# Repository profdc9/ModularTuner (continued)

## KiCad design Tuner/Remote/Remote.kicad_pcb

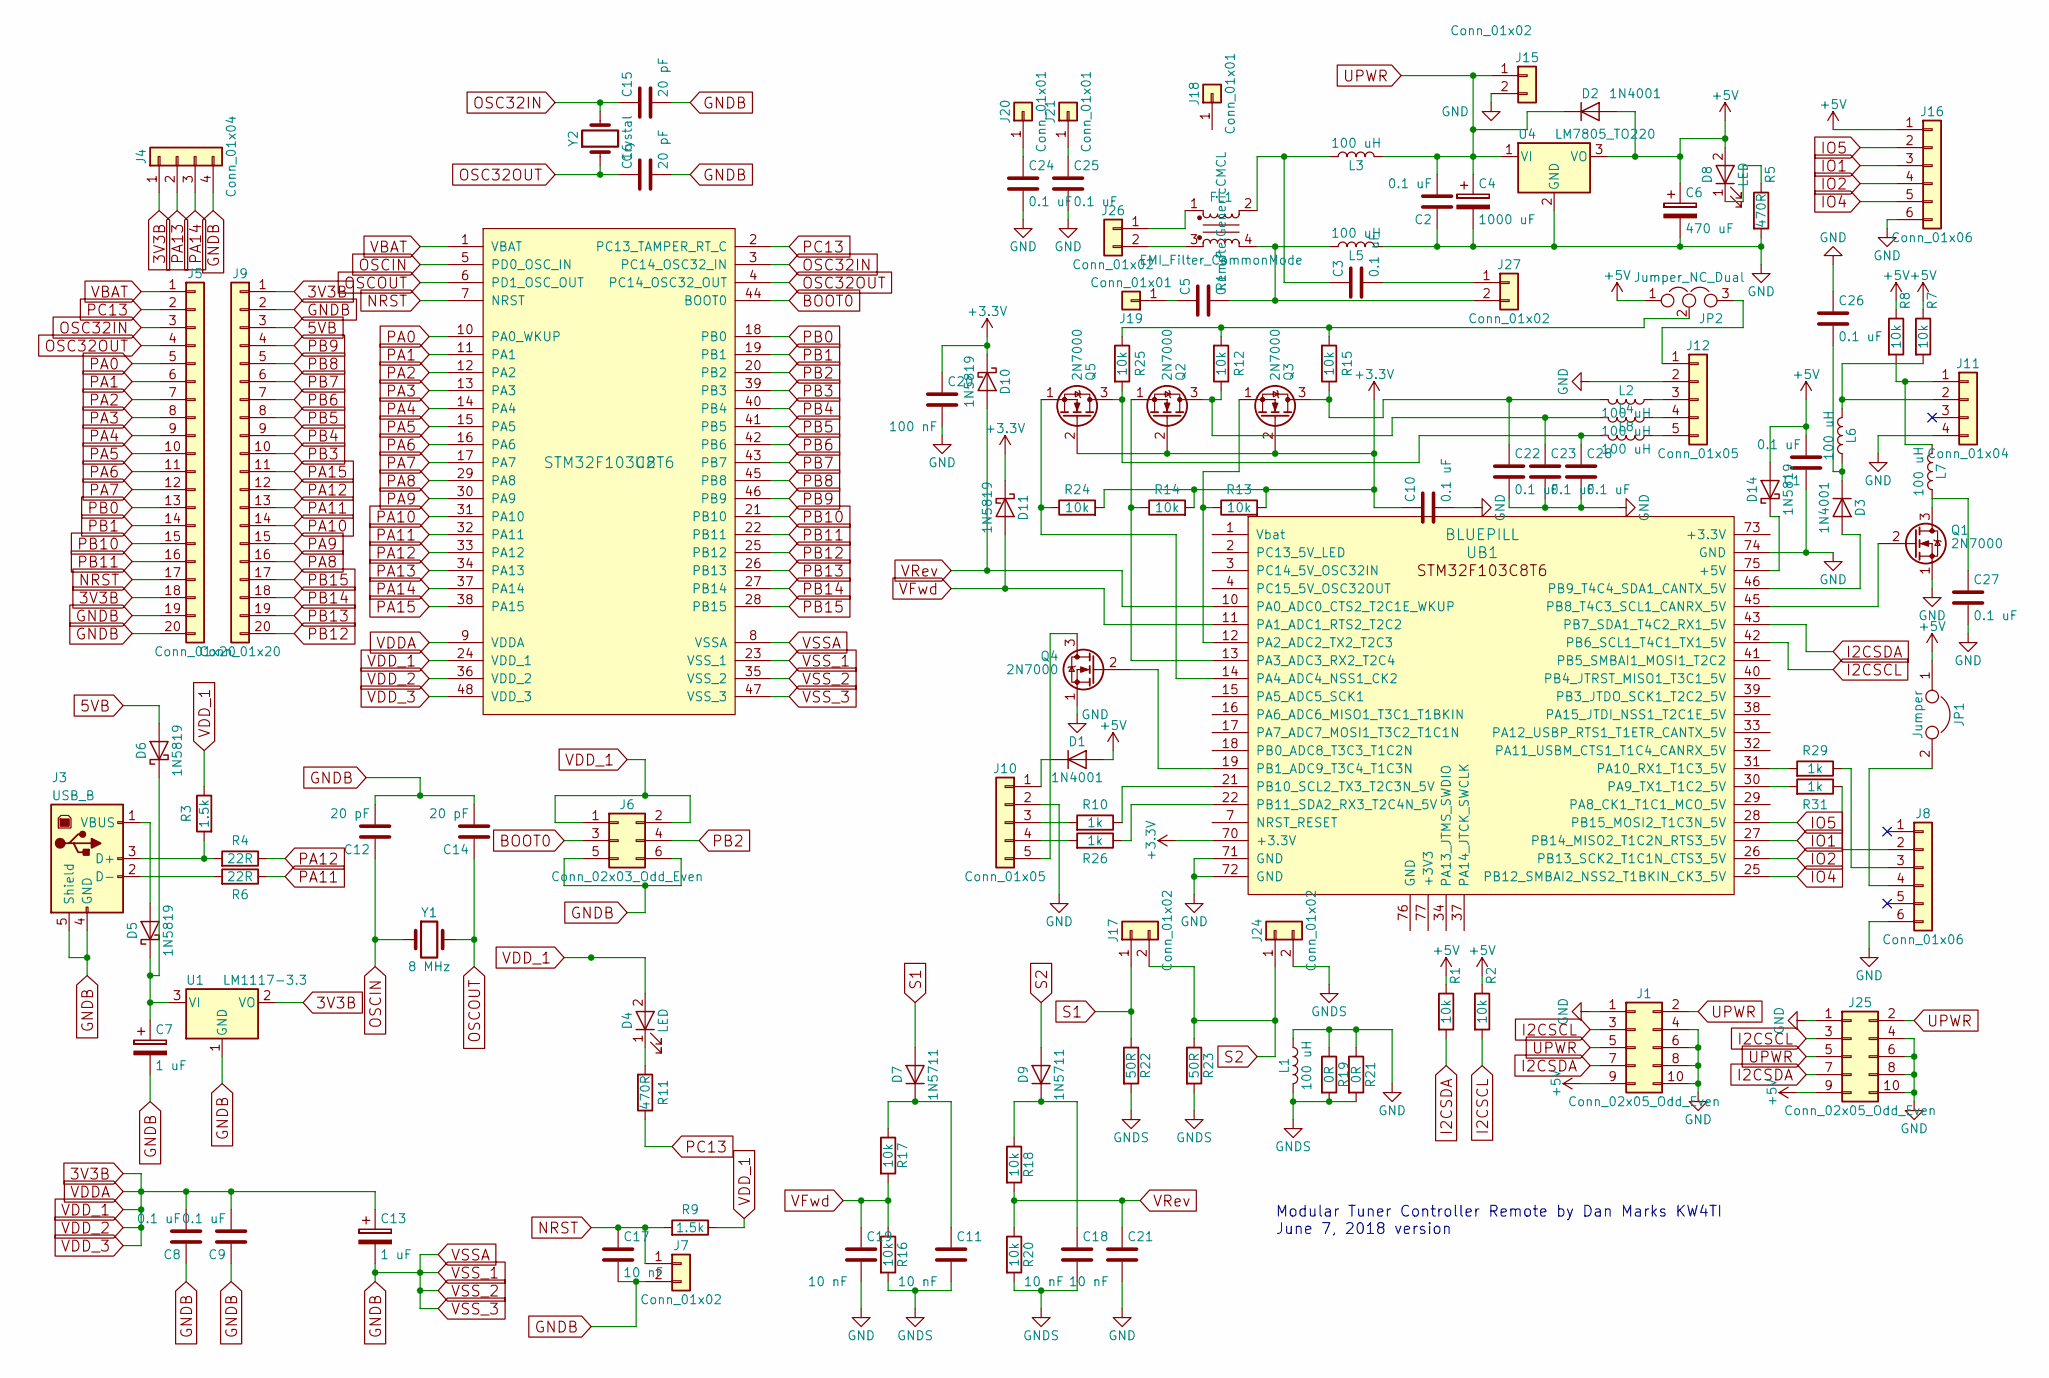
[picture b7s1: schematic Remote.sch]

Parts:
C1, C2, C8, C9, C10, C22, C23, C24, C25, C26, C27, C28: 0.1 uF; C_Disc_D5.0mm_W2.5mm_P2.50mm
C3, C5: 0.1 uF; C_Disc_D12.0mm_W4.4mm_P7.75mm
C4: 1000 uF; CP_Radial_D18.0mm_P7.50mm
C6: 470 uF; CP_Radial_D10.0mm_P5.00mm
C7, C13: 1 uF; CP_Radial_D5.0mm_P2.50mm
C11, C17, C18, C19, C21: 10 nF; C_Disc_D5.0mm_W2.5mm_P2.50mm
C12, C14, C15, C16: 20 pF; C_Disc_D5.0mm_W2.5mm_P2.50mm
C20: 100 nF; C_Disc_D5.0mm_W2.5mm_P2.50mm
D1, D2, D3: 1N4001; D_DO-41_SOD81_P7.62mm_Horizontal
D4: LED; LED_D3.0mm
D5, D6, D10, D11, D14: 1N5819; D_DO-41_SOD81_P7.62mm_Horizontal
D7, D9: 1N5711; D_DO-35_SOD27_P7.62mm_Horizontal
D8: LED; LED_D5.0mm
FL1: EMI_Filter_CommonMode; GenericCMCL
J1, J25: Conn_02x05_Odd_Even; Pin_Header_Straight_2x05_Pitch2.54mm
J3: USB_B
J4, J11: Conn_01x04; Pin_Header_Straight_1x04_Pitch2.54mm
J5, J9: Conn_01x20; Pin_Header_Straight_1x20_Pitch2.54mm
J6: Conn_02x03_Odd_Even; Pin_Header_Straight_2x03_Pitch2.54mm
J7: Conn_01x02; SW_PUSH_6mm
J8, J16: Conn_01x06; Pin_Header_Straight_1x06_Pitch2.54mm
J10, J12: Conn_01x05; Pin_Header_Straight_1x05_Pitch2.54mm
J15, J17, J24, J26, J27: Conn_01x02; TerminalBlock_bornier-2_P5.08mm
J18, J19, J20, J21: Conn_01x01; 1pin
JP1: Jumper; Pin_Header_Straight_1x02_Pitch2.54mm
JP2: Jumper_NC_Dual; Pin_Header_Straight_1x03_Pitch2.54mm
L1: 100 uH; L_Axial_L9.5mm_D4.0mm_P15.24mm_Horizontal_Fastron_SMCC
L2, L4, L6, L7, L8: 100 uH; L_Axial_L5.3mm_D2.2mm_P7.62mm_Horizontal_Vishay_IM-1
L3, L5: 100 uH; L_Toroid_Vertical_L14.0mm_W6.3mm_P4.57mm_Pulse_A
Q1, Q2, Q3, Q4, Q5: 2N7000; TO-92_Molded_Narrow
R1, R2, R7, R8, R12, R13, R14, R15, R16, R17, R18, R20, R24, R25: 10k; R_Axial_DIN0207_L6.3mm_D2.5mm_P7.62mm_Horizontal
R3, R9: 1.5k; R_Axial_DIN0207_L6.3mm_D2.5mm_P7.62mm_Horizontal
R4, R6: 22R; R_Axial_DIN0207_L6.3mm_D2.5mm_P7.62mm_Horizontal
R5, R11: 470R; R_Axial_DIN0207_L6.3mm_D2.5mm_P7.62mm_Horizontal
R10, R26, R29, R31: 1k; R_Axial_DIN0207_L6.3mm_D2.5mm_P7.62mm_Horizontal
R19, R21: 0R; R_Axial_DIN0207_L6.3mm_D2.5mm_P7.62mm_Horizontal
R22, R23: 50R; R_Axial_DIN0309_L9.0mm_D3.2mm_P12.70mm_Horizontal
U1: LM1117-3.3; TO-220-3_Vertical
U2: STM32F103C8T6; LQFP-48_7x7mm_Pitch0.5mm
U4: LM7805_TO220; TO-220-3_Vertical
UB1: BLUEPILL
Y1: 8 MHz; Crystal_HC49-U_Vertical
Y2: Crystal; Crystal_Round_d2.0mm_Vertical

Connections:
3V3B: C8.2, C9.2, C13.1, D4.2 (A), J4.1, J5.18, J6.1, J6.2, J9.1, R3.1, R9.1, U1.2 (VO), U2.9 (VDDA), U2.24 (VDD_1), U2.36 (VDD_2), U2.48 (VDD_3)
5VB: D6.2 (A), J9.3
+3V3: C10.1, C20.1, D10.1 (K), D11.1 (K), Q2.2 (G), Q3.2 (G), Q5.2 (G), R13.2, R14.2, R24.2, UB1.70 (+3.3V)
+5V: C1.2, C6.1, D1.2 (A), D2.2 (A), D8.2 (A), D14.2 (A), J1.9, J16.1, J25.9, JP1.1, JP2.1, R1.1, R2.1, R7.1, R8.1, U4.3 (VO)
BOOT0: J6.3, U2.44 (BOOT0)
GND: C1.1, C2.1, C4.2, C6.2, C10.2, C19.2, C20.2, C21.2, C22.2, C23.2, C24.2, C25.2, C26.1, C27.2, C28.2, J1.1, J1.4, J1.6, J1.8, J1.10, J8.6, J10.2, J11.4, J12.2, J15.2, J16.6, J25.1, J25.4, J25.6, J25.8, J25.10, L1.1, L5.2, Q1.1 (S), Q4.1 (S), R5.2, R19.1, R21.1, U4.2 (GND), UB1.71 (GND), UB1.72 (GND), UB1.74 (GND)
GNDB: C7.2, C8.1, C9.1, C12.2, C13.2, C14.2, C15.2, C16.2, C17.2, J3.4 (GND), J3.5 (Shield), J4.4, J5.19, J5.20, J6.5, J6.6, J7.2, J9.2, U1.1 (GND), U2.8 (VSSA), U2.23 (VSS_1), U2.35 (VSS_2), U2.47 (VSS_3)
GNDS: C11.2, C18.2, J24.2, L1.2, R16.2, R19.2, R20.2, R21.2, R22.2, R23.2
I2CSCL: J1.3, J25.3, R2.2, UB1.42 (PB6_SCL1_T4C1_TX1_5V)
I2CSDA: J1.7, J25.7, R1.2, UB1.43 (PB7_SDA1_T4C2_RX1_5V)
IO1: J16.3, UB1.27 (PB14_MISO2_T1C2N_RTS3_5V)
IO2: J16.4, UB1.26 (PB13_SCK2_T1C1N_CTS3_5V)
IO4: J16.5, UB1.25 (PB12_SMBAI2_NSS2_T1BKIN_CK3_5V)
IO5: J16.2, UB1.28 (PB15_MOSI2_T1C3N_5V)
NRST: C17.1, J5.17, J7.1, R9.2, U2.7 (NRST)
unnamed: C3.1, FL1.2, L3.1
unnamed: C3.2, J27.1
unnamed: C5.1, J19.1
unnamed: C5.2, FL1.4, J27.2, L5.1
unnamed: C7.1, D5.1 (K), D6.1 (K), U1.3 (VI)
unnamed: C11.1, D7.1 (K), R17.1
unnamed: C18.1, D9.1 (K), R18.1
unnamed: C22.1, L2.2, Q3.3 (D), R15.1
unnamed: C23.1, L4.2, Q2.3 (D), R12.1
unnamed: C24.1, J20.1
unnamed: C25.1, J21.1
unnamed: C26.2, D3.1 (K), L6.1
unnamed: C27.1, L7.1, Q1.3 (D)
unnamed: C28.1, L8.2, Q5.3 (D), R25.2
unnamed: D1.1 (K), J10.1
unnamed: D3.2 (A), UB1.46 (PB9_T4C4_SDA1_CANTX_5V)
unnamed: D4.1 (K), R11.2
unnamed: D5.2 (A), J3.1 (VBUS)
unnamed: D8.1 (K), R5.1
unnamed: D14.1 (K), UB1.75 (+5V)
unnamed: FL1.1, J26.1
unnamed: FL1.3, J26.2
unnamed: J3.2 (D-), R6.2
unnamed: J3.3 (D+), R3.2, R4.2
unnamed: J8.2, R31.1
unnamed: J8.3, R29.1
unnamed: J8.4, JP1.2
unnamed: J10.3, R10.2
unnamed: J10.4, R26.2
unnamed: J10.5, Q4.3 (D)
unnamed: J11.1, L7.2, R8.2
unnamed: J11.2, L6.2, R7.2
unnamed: J12.1, JP2.3
unnamed: J12.3, L2.1
unnamed: J12.4, L4.1
unnamed: J12.5, L8.1
unnamed: JP2.2, R12.2, R15.2, R25.1
unnamed: Q1.2 (G), UB1.45 (PB8_T4C3_SCL1_CANRX_5V)
unnamed: Q2.1 (S), R14.1, UB1.13 (PA3_ADC3_RX2_T2C4)
unnamed: Q3.1 (S), R13.1, UB1.12 (PA2_ADC2_TX2_T2C3)
unnamed: Q4.2 (G), UB1.19 (PB1_ADC9_T3C4_T1C3N)
unnamed: Q5.1 (S), R24.1, UB1.14 (PA4_ADC4_NSS1_CK2)
unnamed: R10.1, UB1.21 (PB10_SCL2_TX3_T2C3N_5V)
unnamed: R26.1, UB1.22 (PB11_SDA2_RX3_T2C4N_5V)
unnamed: R29.2, UB1.31 (PA10_RX1_T1C3_5V)
unnamed: R31.2, UB1.30 (PA9_TX1_T1C2_5V)
OSC32IN: C15.1, J5.3, U2.3 (PC14_OSC32_IN), Y2.2
OSC32OUT: C16.1, J5.4, U2.4 (PC14_OSC32_OUT), Y2.1
OSCIN: C12.1, U2.5 (PD0_OSC_IN), Y1.1
OSCOUT: C14.1, U2.6 (PD1_OSC_OUT), Y1.2
PA0: J5.5, U2.10 (PA0_WKUP)
PA1: J5.6, U2.11 (PA1)
PA2: J5.7, U2.12 (PA2)
PA3: J5.8, U2.13 (PA3)
PA4: J5.9, U2.14 (PA4)
PA5: J5.10, U2.15 (PA5)
PA6: J5.11, U2.16 (PA6)
PA7: J5.12, U2.17 (PA7)
PA8: J9.16, U2.29 (PA8)
PA9: J9.15, U2.30 (PA9)
PA10: J9.14, U2.31 (PA10)
PA11: J9.13, R6.1, U2.32 (PA11)
PA12: J9.12, R4.1, U2.33 (PA12)
PA13: J4.2, U2.34 (PA13)
PA14: J4.3, U2.37 (PA14)
PA15: J9.11, U2.38 (PA15)
PB0: J5.13, U2.18 (PB0)
PB1: J5.14, U2.19 (PB1)
PB2: J6.4, U2.20 (PB2)
PB3: J9.10, U2.39 (PB3)
PB4: J9.9, U2.40 (PB4)
PB5: J9.8, U2.41 (PB5)
PB6: J9.7, U2.42 (PB6)
PB7: J9.6, U2.43 (PB7)
PB8: J9.5, U2.45 (PB8)
PB9: J9.4, U2.46 (PB9)
PB10: J5.15, U2.21 (PB10)
PB11: J5.16, U2.22 (PB11)
PB12: J9.20, U2.25 (PB12)
PB13: J9.19, U2.26 (PB13)
PB14: J9.18, U2.27 (PB14)
PB15: J9.17, U2.28 (PB15)
PC13: J5.2, R11.1, U2.2 (PC13_TAMPER_RT_C)
S1: D7.2 (A), J17.1, R22.1
S2: D9.2 (A), J17.2, J24.1, R23.1
UPWR: C2.2, C4.1, D2.1 (K), J1.2, J1.5, J15.1, J25.2, J25.5, L3.2, U4.1 (VI)
VBAT: J5.1, U2.1 (VBAT)
VFwd: C19.1, D11.2 (A), R16.1, R17.2, UB1.11 (PA1_ADC1_RTS2_T2C2)
VRev: C21.1, D10.2 (A), R18.2, R20.1, UB1.10 (PA0_ADC0_CTS2_T2C1E_WKUP)

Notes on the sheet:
Modular Tuner Controller Remote by Dan Marks KW4TI June 7, 2018 version

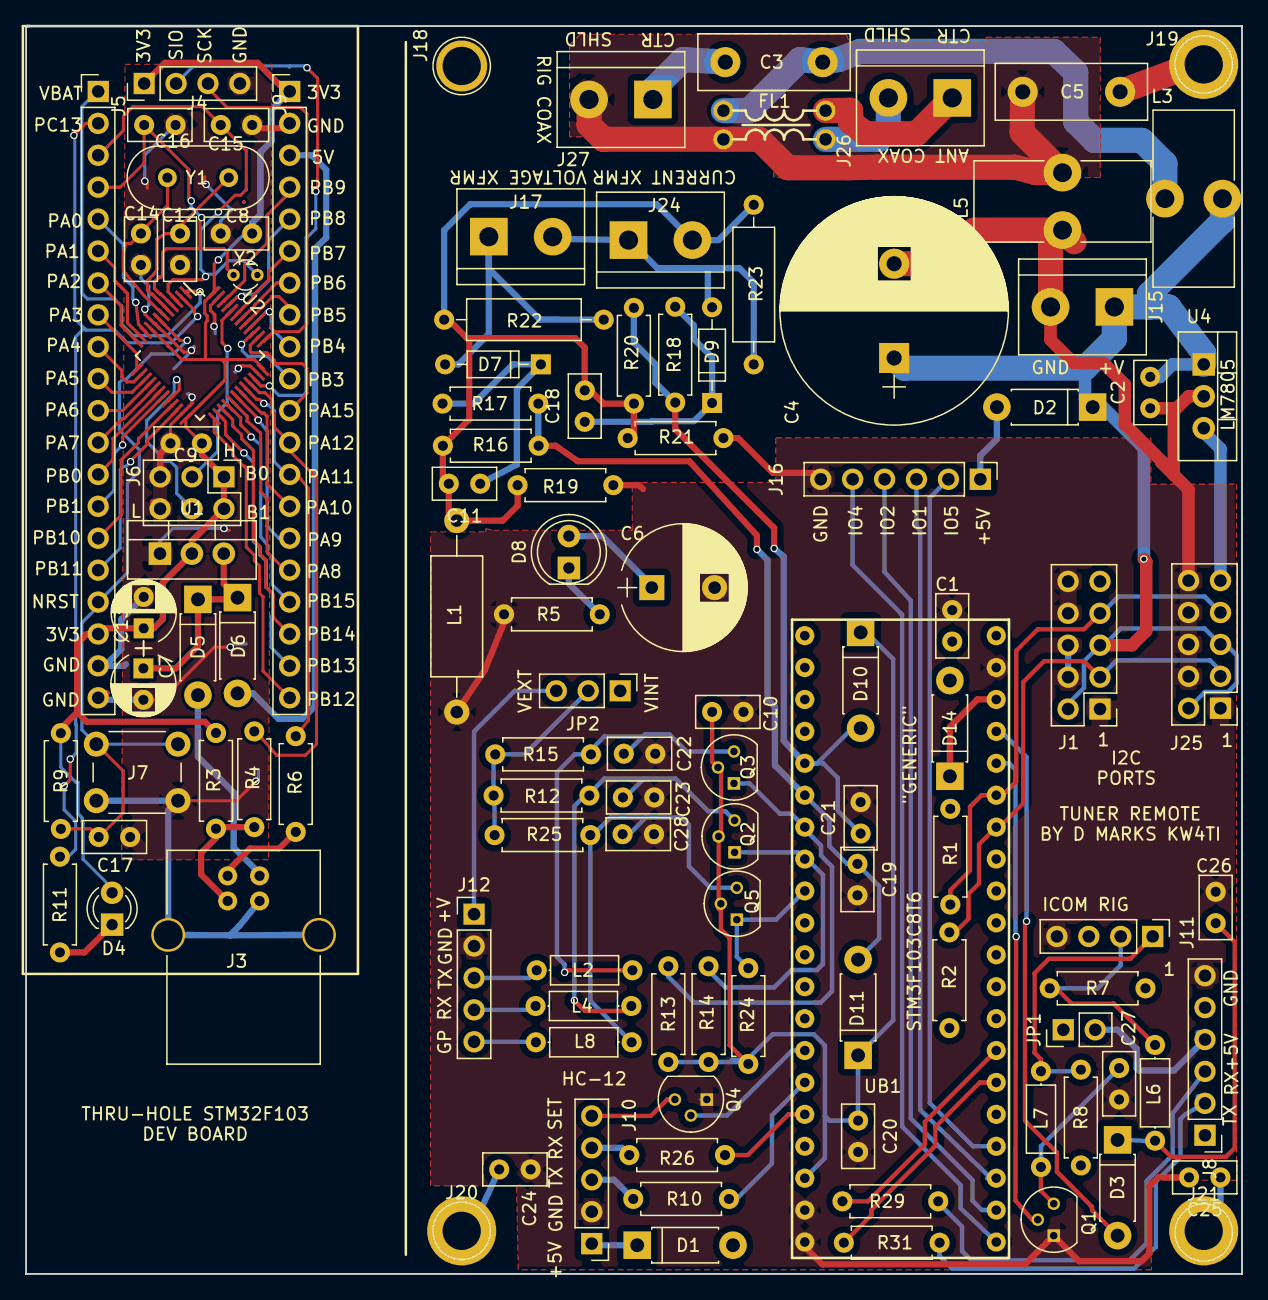
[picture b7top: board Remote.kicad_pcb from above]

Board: 2 copper layers, 96.8 x 99.3 mm, 112 parts (0 on the bottom side), 104 nets.
